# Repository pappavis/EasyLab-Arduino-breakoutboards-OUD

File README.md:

# EasyLab-Arduino-breakoutboards-OUD
Arduino breakout boards vir IOT testing
<br/>

KiCAD model vir Arduino prototyping breakout shield.<br/>
<br/>
Ontwerp: Michiel Erasmus<br/>
Nov-2015<br/>
<br/>
<br/>
<br/>

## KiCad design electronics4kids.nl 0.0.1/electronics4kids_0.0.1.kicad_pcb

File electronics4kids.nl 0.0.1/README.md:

KiCAD printplaat vir IoT bord<br/>
<br/>
Ontwerp: Michiel Erasmus<br/>
Nov-2015<br/>
<br/>
<br/>
<br/>

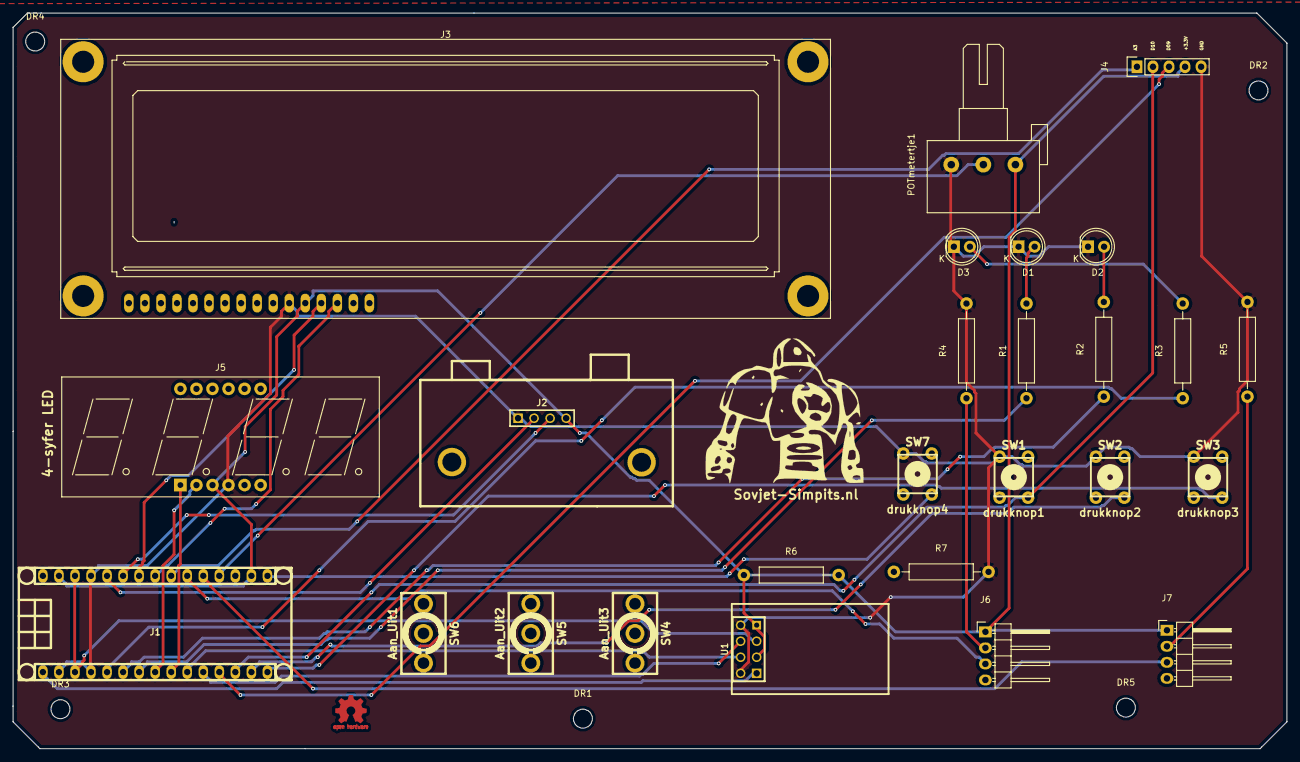
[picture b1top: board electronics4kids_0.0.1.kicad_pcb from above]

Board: 2 copper layers, 201.8 x 116.5 mm, 32 parts (0 on the bottom side), 29 nets.

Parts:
D1: LED3; LED-5MM
D2: LED2; LED-5MM
D3: LED1; LED-5MM
DR1: Gaatje1; MountingHole_3mm
DR2: Gaatje2; MountingHole_3mm
DR3: Gaatje5; MountingHole_3mm
DR4: Gaatje3; MountingHole_3mm
DR5: Gaatje4; MountingHole_3mm
DR6: Sovjet simpits; LOGO-sovjetSimpits
J1: Arduino_Nano_V3; arduino_nano_header
J2: HC-SR04 afstandmeter; HC-SR04
J3: I2C LCD 1602 HD44780; LCD-016N002L
J4: HDR_5_Algemeen IO; Pin_Header_Straight_1x05
J5: 4-syfer LED MAX7219; Cx56-12
J6: Pressure sensor; Pin_Header_Angled_1x04
J7: DHT11 Vochtmeting; Pin_Header_Angled_1x04
POTmetertje1: POTmeter; Potentiometer_Alps-RK163-single_15mm
R1, R2, R3, R4, R5, R7: R1k; Resistor_Horizontal_RM15mm
R6: R10k; Resistor_Horizontal_RM15mm
SW1: drukknop1; PCB_PUSH
SW2: drukknop2; PCB_PUSH
SW3: drukknop3; PCB_PUSH
SW4: Aan_Uit3; switch_100sp5
SW5: Aan_Uit2; switch_100sp5
SW6: Aan_Uit1; switch_100sp5
SW7: drukknop4; PCB_PUSH
U1: ESP-01v090; ESP8266_MODULE

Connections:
+3.3V: J1.17, J1.29, J2.4, J3.3, J4.4, J5.3, J6.1, J7.1, POTmetertje1.1, R6.1, R6.2, U1.3, U1.7
/A0: J1.19, POTmetertje1.2
/A1: J1.20, J7.3
/A2: J1.21, J6.3
/A3: J1.22, J4.1
/A6: J1.25, J2.3
/A7: J1.26, J2.2
/D02: J1.5, R3.1
/D03: J1.6, R2.1
/D04: J1.7, R1.1
/D05: J1.8, J5.2
/D06: J1.9, J5.1
/D07: J1.10, U1.4
/D08: J1.11, U1.6
/D09: J1.12, J4.3
/D10: J1.13, J4.2, SW1.2
/D11: J1.14, SW2.2
/D12: J1.15, SW3.2
/D13: J1.16, SW7.2
/RST: J1.3, J1.28, U1.5
/SCL: J1.23, J3.1
/SDA: J1.24, J3.2
/TX: J1.1, U1.1
GND: D1.1, D2.1, D3.1, J1.2, J1.4, J1.27, J2.1, J3.4, J4.5, J5.4, POTmetertje1.3, R4.2, R5.2, R7.2, SW1.1, SW2.1, SW3.1, SW7.1, U1.2, U1.8
unnamed: D1.2, R1.2
unnamed: D2.2, R2.2
unnamed: D3.2, R3.2
unnamed: J6.2, R4.1
unnamed: J7.2, R5.1

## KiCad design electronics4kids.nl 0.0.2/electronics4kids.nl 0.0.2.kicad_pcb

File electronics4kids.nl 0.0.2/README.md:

breakout bord<br/>
Ontwerp: Michiel Erasmus<br/>
<br/>
<br/>
<br/>

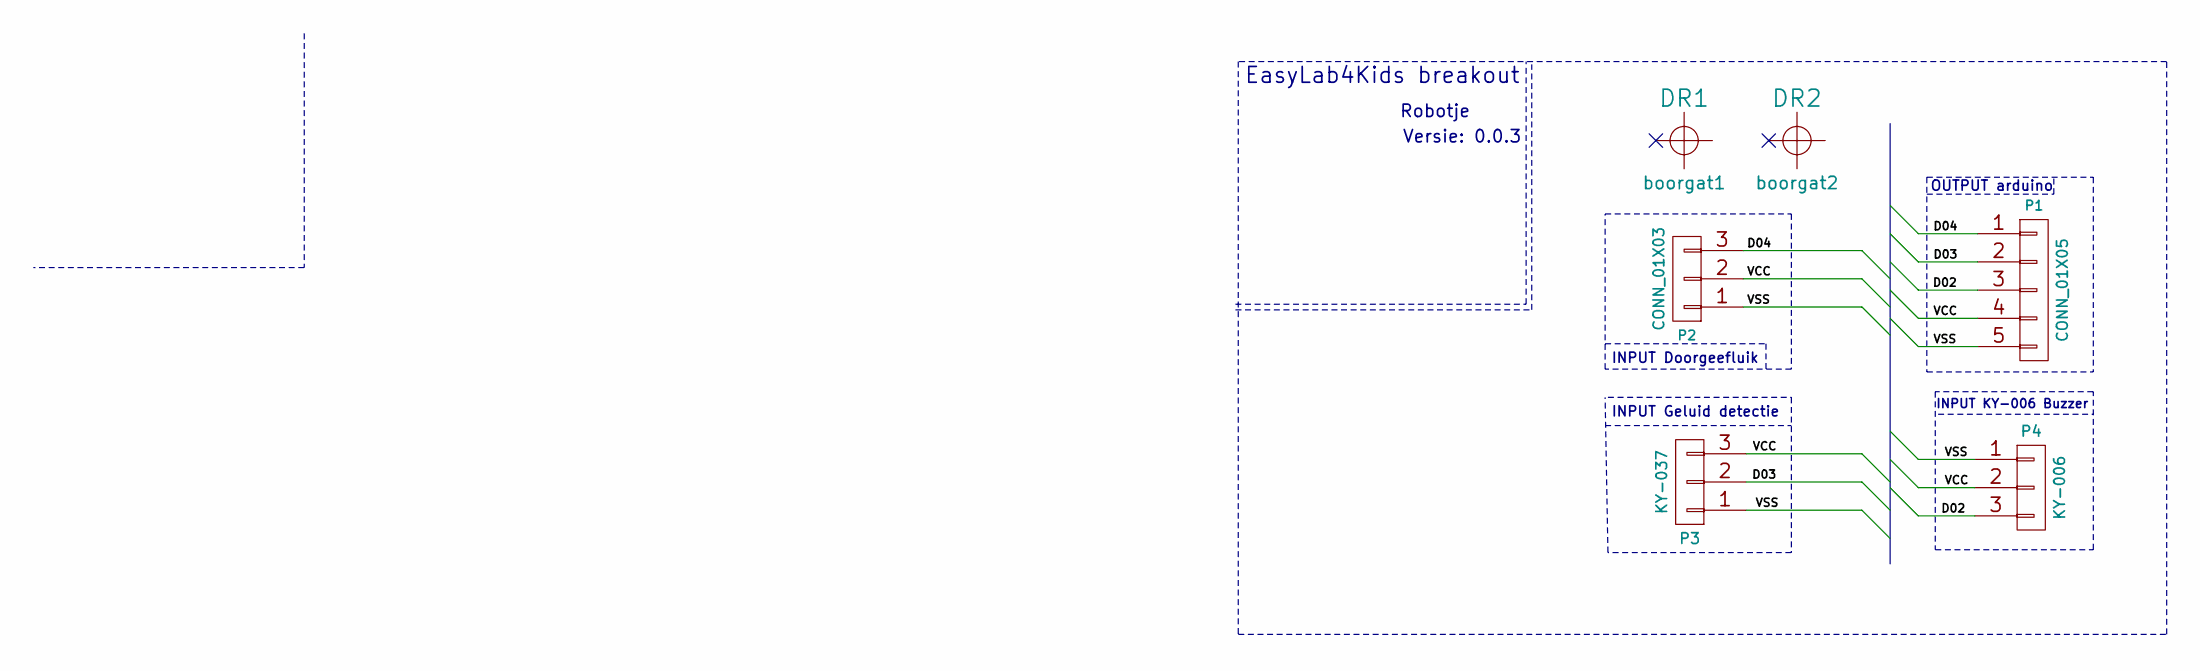
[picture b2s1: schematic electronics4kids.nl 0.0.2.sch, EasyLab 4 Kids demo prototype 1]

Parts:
DR1: boorgat1; hole_5mm
DR2: boorgat2; hole_5mm
P1: CONN_01X05; Socket_Strip_Angled_1x05
P2: CONN_01X03; Socket_Strip_Angled_1x03
P3: KY-037; Socket_Strip_Straight_1x03
P4: KY-006; Socket_Strip_Straight_1x03

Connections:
/D02: P1.3, P4.3
/D03: P1.2, P3.2
/D04: P1.1, P2.3
/VCC: P1.4, P2.2, P3.3, P4.2
/VSS: P1.5, P2.1, P3.1, P4.1

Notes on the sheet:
EasyLab4Kids breakout
Versie: 0.0.3
Robotje
INPUT KY-006 Buzzer
INPUT Geluid detectie
INPUT Doorgeefluik
OUTPUT arduino

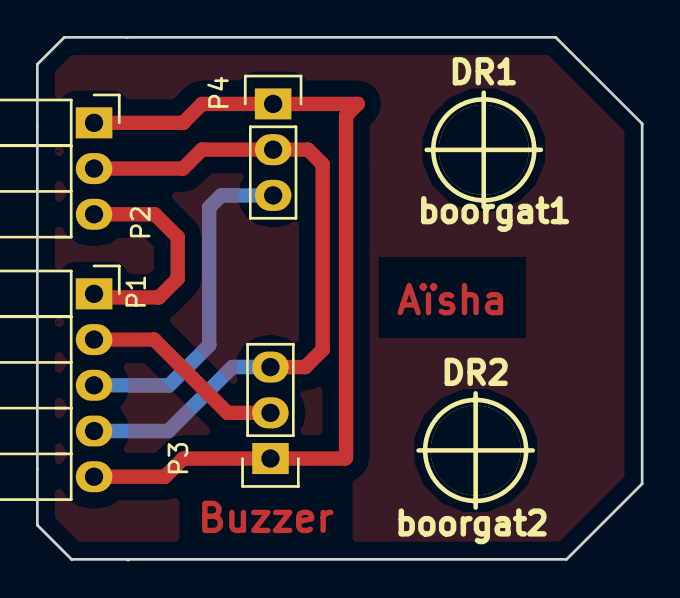
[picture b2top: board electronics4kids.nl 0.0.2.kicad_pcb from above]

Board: 2 copper layers, 33.6 x 29.0 mm, 6 parts (0 on the bottom side), 5 nets.

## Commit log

2018-04-05 eerste commit

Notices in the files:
electronics4kids.nl 0.0.1/electronics4kids_0.0.1.kicad_pcb:
©2016 Spvjet Simpits.nl
